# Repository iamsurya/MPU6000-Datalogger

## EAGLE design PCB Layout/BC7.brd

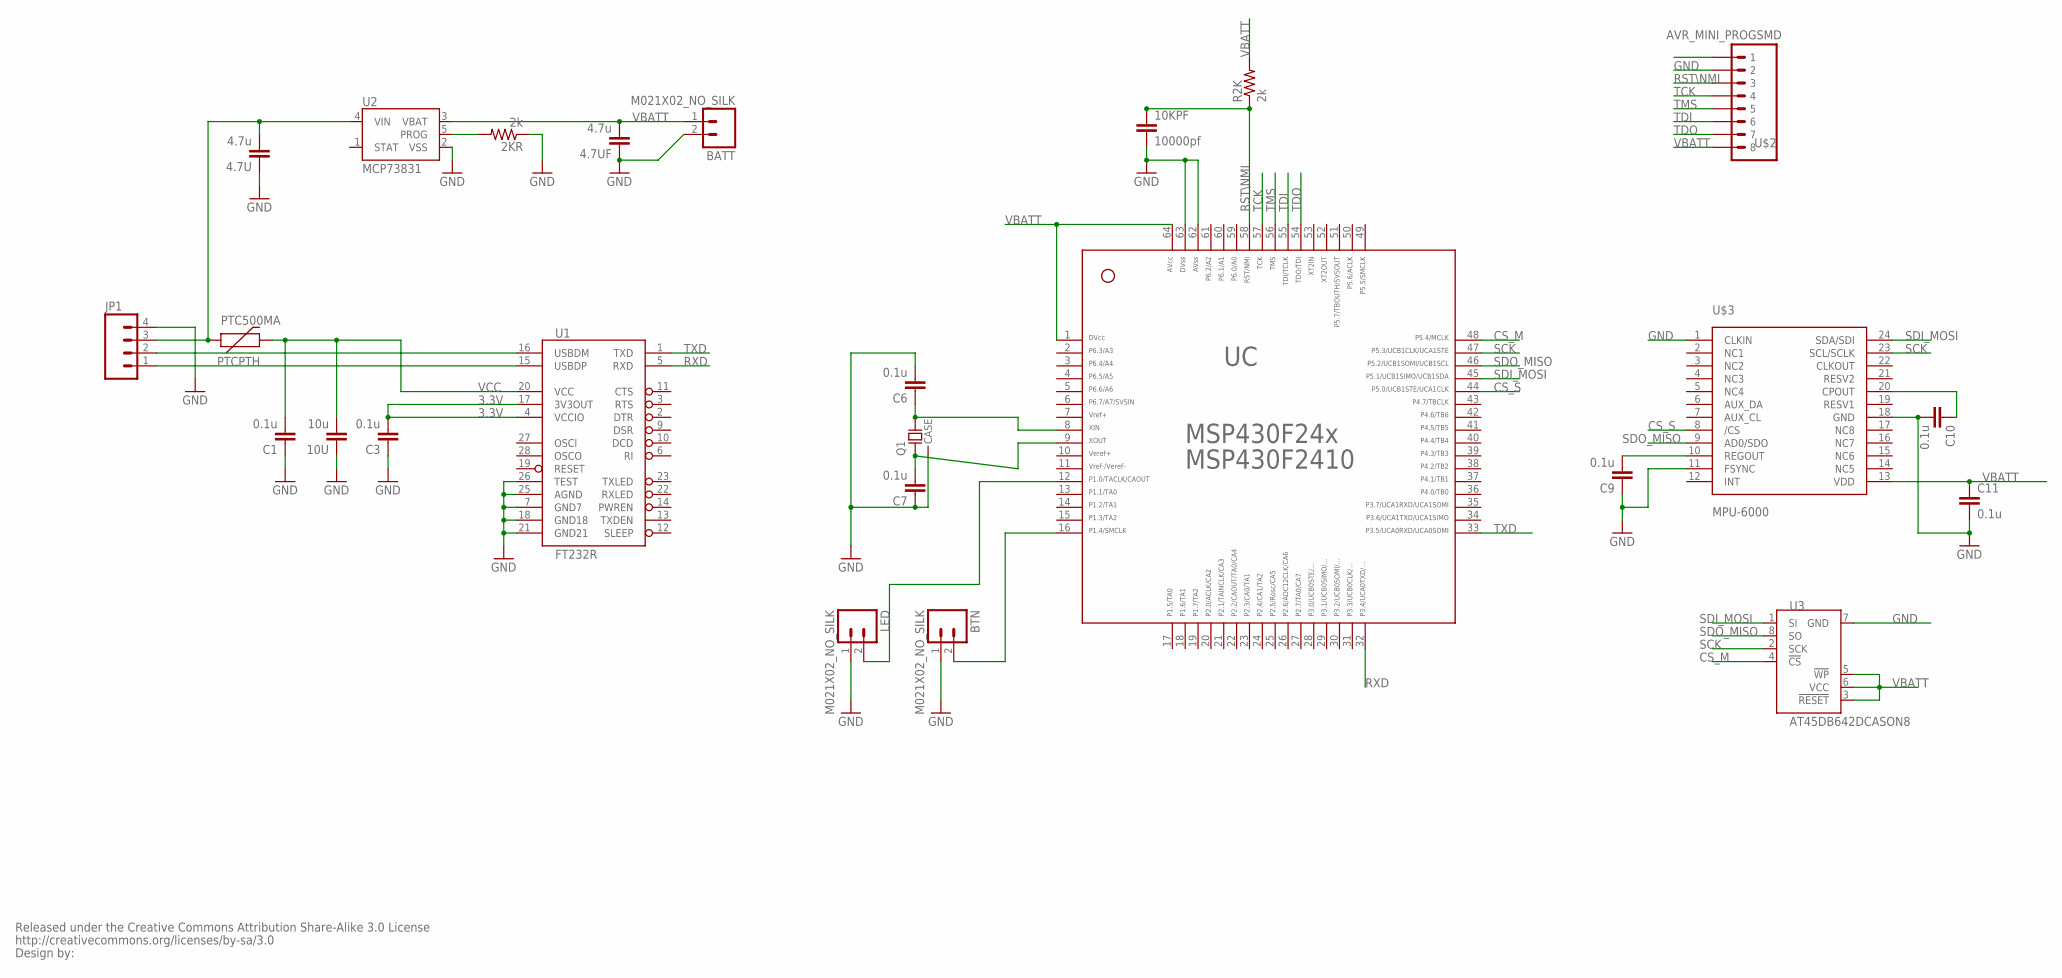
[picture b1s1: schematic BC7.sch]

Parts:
2KR: 2k; 0402-RES
4.7U, 4.7UF: 4.7u; 0402-CAP
10KPF: 10000pf; CAP-PTH-SMALLEZ
10U: 10u; 0402-CAP
BATT: M021X02_NO_SILK; 1X02_NO_SILK
BTN: M021X02_NO_SILK; 1X02_NO_SILK
C1, C3, C6, C7, C9, C10, C11: 0.1u; 0402-CAP
JP1: M04LOCK; 1X04_LOCK
LED: M021X02_NO_SILK; 1X02_NO_SILK
PTC500MA: PTCPTH; PTC
Q1: MS1V-T1K-32.768KHZ/12.5PF/20PPM/TA/QC; MS1V-T1K
R2K: 2k; 0204/5
U1: FT232R; SSOP28DB
U2: MCP73831; SOT23-5
U3: AT45DB642DCASON8; CASON8
U$1: CREATIVE_COMMONS
U$2: AVR_MINI_PROGSMD; AVR_MINI_PROG
U$3: MPU-6000; QFN-24
UC: F24[X/10]---PM64; PM/PAG64

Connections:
3.3V: C3.2, U1.4 (VCCIO), U1.17 (3V3OUT)
5V: 4.7U.2, JP1.3, PTC500MA.P$1 (1), U2.4 (VIN)
BTN: BTN.2, UC.16
CS_M: U3.4 (!CS), UC.48
CS_S: U$3.8 (/CS), UC.44
GND: 2KR.1, 4.7U.1, 4.7UF.1, 10KPF.2, 10U.1, BATT.2, BTN.1, C1.1, C3.1, C6.2, C7.1, C9.1, C10.2, C11.2, JP1.4, LED.1, Q1.CASE, U1.7 (GND7), U1.18 (GND18), U1.21 (GND21), U1.25 (AGND), U1.26 (TEST), U2.2 (VSS), U3.7 (GND), U$2.2, U$3.1 (CLKIN), U$3.11 (FSYNC), U$3.18 (GND), UC.62, UC.63
unnamed: LED.2, UC.12
unnamed: 2KR.2, U2.5 (PROG)
unnamed: C6.1, Q1.2, UC.8
unnamed: C7.2, Q1.1, UC.9
unnamed: C9.2, U$3.10 (REGOUT)
unnamed: C10.1, U$3.20 (CPOUT)
RST\NMI: 10KPF.1, R2K.1, U$2.3, UC.58
RXD: U1.5 (RXD), UC.32
SCK: U3.2 (SCK), U$3.23 (SCL/SCLK), UC.47
SDI_MOSI: U3.1 (SI), U$3.24 (SDA/SDI), UC.45
SDO_MISO: U3.8 (SO), U$3.9 (AD0/SDO), UC.46
TCK: U$2.4, UC.57
TDI: U$2.6, UC.55
TDO: U$2.7, UC.54
TMS: U$2.5, UC.56
TXD: U1.1 (TXD), UC.33
USB_D+: JP1.1, U1.15 (USBDP)
USB_D-: JP1.2, U1.16 (USBDM)
VBATT: 4.7UF.2, BATT.1, C11.1, R2K.2, U2.3 (VBAT), U3.3 (!RESET), U3.5 (!WP), U3.6 (VCC), U$2.8, U$3.13 (VDD), UC.1, UC.64
VCC: 10U.2, C1.2, PTC500MA.P$2 (2), U1.20 (VCC)

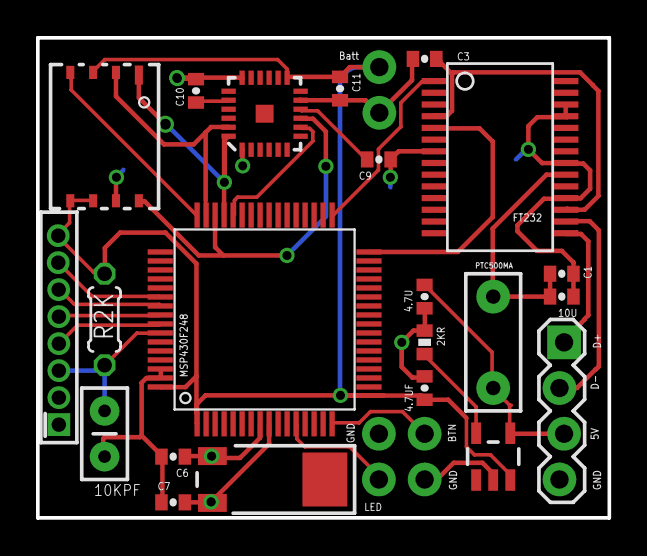
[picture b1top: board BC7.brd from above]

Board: 2 copper layers, 31.8 x 26.7 mm, 26 parts (0 on the bottom side), 26 nets.

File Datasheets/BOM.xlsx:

Part | Value | Device | Package | Description | DATASHEET | LINK | MFGPN | PROD_ID
2KR | 2k | RESISTOR0402-RES | 0402-RES | Resistor
R2K | 2k | R-US_0204/5 | 0204/5 | RESISTOR, American symbol
4.7U | 4.7u | CAP0402-CAP | 0402-CAP | Capacitor
4.7UF | 4.7u | CAP0402-CAP | 0402-CAP | Capacitor
10KPF | 10000pf | CAPEZ | CAP-PTH-SMALLEZ | Capacitor
10U | 10u | CAP0402-CAP | 0402-CAP | Capacitor
C1 | 0.1u | CAP0402-CAP | 0402-CAP | Capacitor
C3 | 0.1u | CAP0402-CAP | 0402-CAP | Capacitor
C6 | 0.1u | CAP0402-CAP | 0402-CAP | Capacitor
C7 | 0.1u | CAP0402-CAP | 0402-CAP | Capacitor
C9 | 0.1u | CAP0402-CAP | 0402-CAP | Capacitor
C10 | 0.1u | CAP0402-CAP | 0402-CAP | Capacitor
C11 | 0.1u | CAP0402-CAP | 0402-CAP | Capacitor
PTC500MA | PTCPTH | PTCPTH | PTC | Resettable Fuse PTC
Q1 |  | 32768Hz Crystal | MS1V-T1K | p r e l i m i n a r y 5 . 0 . 0
U$3 | MPU-6000 | MPU-6000 | QFN-24 | Invensense MPU-6000: 3-axis gyro, 3-axis accel & 9-axis MotionFusion | http://invensense.com/mems/gyro/documents/PS-MPU-6000A-00_v1.0.pdf | http://invensense.com/mems/gyro/mpu6000.html | MPU-6000
U1 | FT232R | FT232RLSSOP | SSOP28DB | USB UART
U2 | MCP73831 | MCP73831 | SOT23-5 | Miniature single cell, fully integrated Li-Ion, Li-polymer charge management co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 |  |  |  | IC-09995
U3 | AT45DB642DCASON8 | AT45DB642DCASON8 | CASON8 | at45db642d memory CASON8
UC | MSP430F248 | MSP430F248 F24[X/10]---PM64 | PM/PAG64 | ***MSP430F24[x/10]***PM64
BATT | M021X02_NO_SILK | M021X02_NO_SILK | 1X02_NO_SILK | Standard 2-pin 0.1 header. Use with"
BTN | M021X02_NO_SILK | M021X02_NO_SILK | 1X02_NO_SILK | Standard 2-pin 0.1 header. Use with"
JP1 |  | M04LOCK | 1X04_LOCK | Header 4
LED | M021X02_NO_SILK | M021X02_NO_SILK | 1X02_NO_SILK | Standard 2-pin 0.1 header. Use with"
U$2 | AVR_MINI_PROGSMD | AVR_MINI_PROGSMD | AVR_MINI_PROG | AVR ISP 6-pin inline header

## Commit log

2014-04-13 Init Empty Files
2014-04-16 Complete Commit. Reads MPU6000 data.
    Has extra functions to read / write memory.
2014-04-16 Added .gitignore
2014-04-17 Cleaned Version Reads and Wries to Memory at 15hz
    Need to add reading from memory and sending over uart
2014-04-17 Fixing .gitignore
2014-04-19 Changed SPI from Port 3 to Port 5
    Having UART on the Same Port would require initializing pins to SPI and
    then to UART back and forth when reading from memory. Avoided this by
    having them on different ports. USCI_Ax is only on P3.
2014-04-19 Added UART
    Added UART to the device
2014-04-22 Fixed UART sending only first page repeatedly
2014-04-28 Multiple Fixes
    Fixed the Address sent to the Dataflash. ( It has to leave the highest
    bit when in 1024 mode).
    Fixed Sending the Time when logging in ASCII.
    Changed from ASCII to Binary Mode logging.
2014-04-28 Removed Unwanted Code. Changed UART to 115200 bps.
2014-04-28 Removed delays in SPI fns, moved unwated fn's
    to .h
2014-04-29 Removed extra whitespace. Fixed timer drift.
2014-05-01 Changed Button Behaviour
    OFF : Short Button Press: Turn ON
    OFF: Long Press : Reset Page Counter
    ON : Short Press : Do Nothing
    ON : Long Press : Turn OFF
2014-05-21 Random Commit
    Will revert after this.
2014-05-21 Added read device data by UART RX
    Send 's', 'd' to the device for a memory dump.
2014-05-23 Read and Write the page number to Flash
2014-10-11 Small Changes
    Memory is dumped in binary.
2015-02-05 BCDumer Update
    Sends number of pages and the 'nc' command to the windows app
2015-02-10 BCDumper Full Update
    Works with BCDumper to Dump Data.
2015-02-11 TimeSyncCommit
2015-02-11 Committing Good Syncing Code
2015-02-11 Fixing Github Mess up
2015-02-11 Removing Files not needed.
2015-02-11 ignore
2015-02-11 Removing more files
2015-02-11 Github won't ignore files.
2015-02-18 Working copy with Checktime and SyncTime
2015-03-23 SVS set o 3.05V and Bugfixes
2015-04-17 Small bugFix
2018-02-04 Set theme jekyll-theme-minimal
2018-02-04 Changing folder layout to add non-code files
    To do:
    Add Eagle PCB files, datasheets, thesis and presentation.
2018-02-04 Moving Readme.md for github pages
2018-02-04 Added PCB Layout designed using Eagle PCB
2018-02-04 Added datasheets, thesis and presentation pdf
2018-02-04 Image showing final device and parts added

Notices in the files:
parts and their libraries:
SparkFun: Released under the Creative Commons Attribution Share-Alike 3.0 License
SparkFun: http://creativecommons.org/licenses/by-sa/3.0
SparkFun-Connectors: Licensing: CC v3.0 Share-Alike You are welcome to use this library for commercial purposes.
